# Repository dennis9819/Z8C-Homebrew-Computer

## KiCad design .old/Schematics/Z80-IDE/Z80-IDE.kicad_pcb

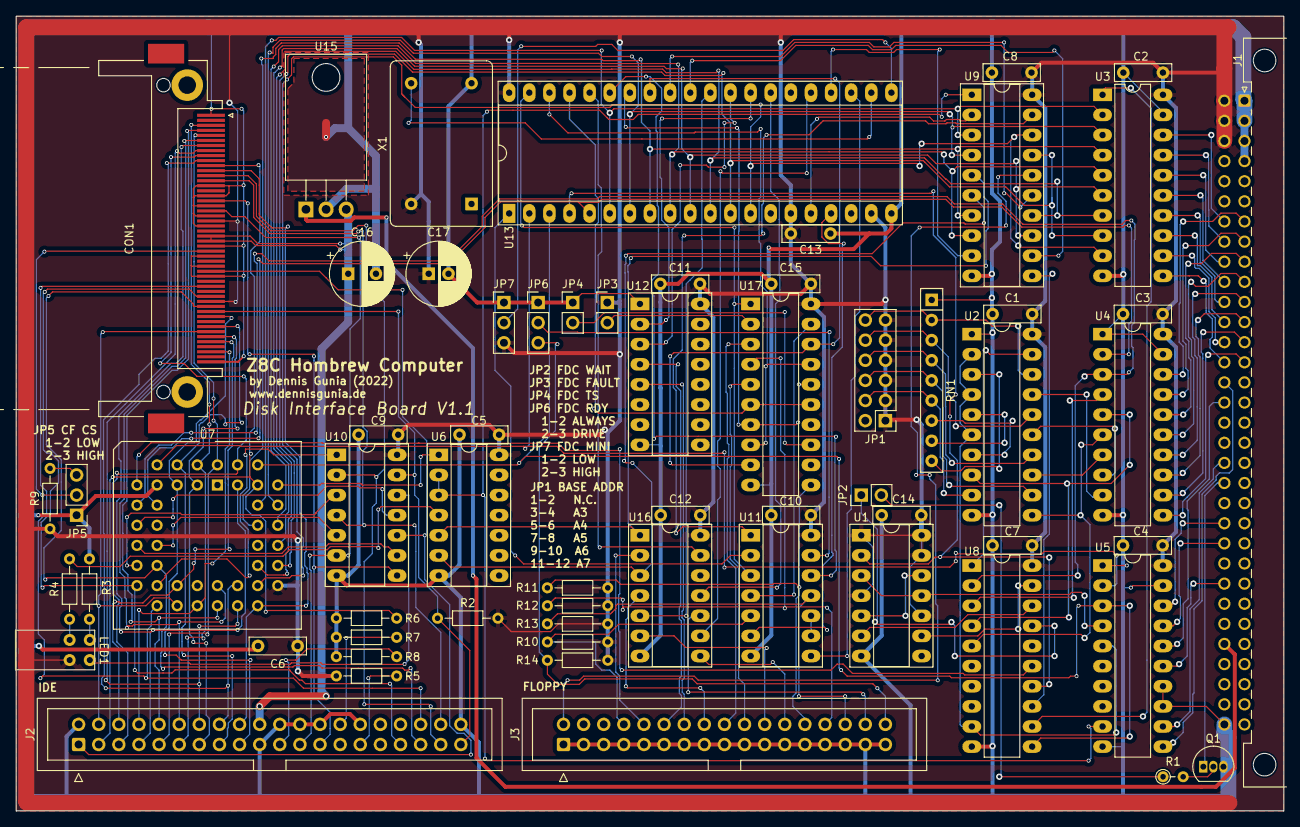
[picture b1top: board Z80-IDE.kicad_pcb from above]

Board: 2 copper layers, 160.0 x 100.3 mm, 62 parts (0 on the bottom side), 151 nets.

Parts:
C1, C2, C3, C4, C5, C6, C7, C8, C9, C10, C11, C12, C13, C14, C15: 100nF; C_Rect_L7.0mm_W2.0mm_P5.00mm
C16: 470uF; CP_Radial_D8.0mm_P3.50mm
C17: 100uF; CP_Radial_D8.0mm_P2.50mm
CON1: CF-CARD; CF-Card_3M_N7E50-E516xx-30
J1: Conn_02x32_Row_Letter_First; DIN41612_Q_2x32_Male_Horizontal_THT
J2: IDE Connector; IDC-Header_2x20_P2.54mm_Vertical
J3: Floppy Connector; IDC-Header_2x17_P2.54mm_Vertical
JP1: Conn_02x06_Odd_Even; PinHeader_2x06_P2.54mm_Vertical
JP2, JP3, JP4: Jumper_2_Bridged; PinHeader_1x02_P2.54mm_Vertical
JP5, JP6, JP7: Jumper_3_Open; PinHeader_1x03_P2.54mm_Vertical
LED1: MENOTR_A500_Dual_3mm; MENTOR A500 Dual 3mm
Q1: BC548; TO-92_Inline
R1: 220; R_Axial_DIN0204_L3.6mm_D1.6mm_P2.54mm_Vertical
R2, R3, R4, R5, R6, R7, R8, R9, R10, R11, R12, R13, R14: 10k; R_Axial_DIN0204_L3.6mm_D1.6mm_P7.62mm_Horizontal
RN1: R_Network08; R_Array_SIP9
U1: 74HC74; DIP-14_W7.62mm_Socket_LongPads
U2: 74LS688; DIP-20_W7.62mm_LongPads
U3, U4, U5: 74HC245; DIP-20_W7.62mm_LongPads
U6: 74HC02; DIP-14_W7.62mm_Socket_LongPads
U7: 82C55A_PLCC; PLCC-44_THT-Socket
U8: GAL16V8; DIP-20_W7.62mm_LongPads
U9: 74HCT273; DIP-20_W7.62mm_Socket_LongPads
U10, U16: 74HCT04; DIP-14_W7.62mm_Socket_LongPads
U11: 74HCT14; DIP-14_W7.62mm_Socket_LongPads
U12: 74HCT139; DIP-16_W7.62mm_Socket_LongPads
U13: FDC9266; DIP-40_W15.24mm_Socket_LongPads
U15: L7805; TO-220-3_Horizontal_TabDown
U17: 74HC240; DIP-20_W7.62mm_LongPads
X1: 8MHz; Oscillator_DIP-14

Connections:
+5V: C1.1, C2.1, C3.1, C4.1, C5.1, C6.1, C7.1, C8.1, C9.1, C10.1, C11.1, C12.1, C13.1, C14.1, C15.1, C17.1, CON1.36 (/WE), CON1.44 (/REG), J1.b1, J1.b2, J1.b3, JP1.1, JP1.3, JP1.5, JP1.7, JP1.9, JP1.11, JP3.1 (A), JP7.3 (B), LED1.2b (A), R2.2, R5.1, R9.1, R10.2, R11.2, R12.2, R13.2, R14.2, U1.1 (~R), U1.4 (~S), U1.10 (~S), U1.13 (~R), U1.14 (VCC), U2.20 (VCC), U3.20 (VCC), U4.20 (VCC), U5.20 (VCC), U6.14 (VCC), U7.29 (VCC), U8.20 (VCC), U9.20 (VCC), U10.14 (VCC), U11.14 (VCC), U12.16 (VCC), U13.15 (~DACK), U13.19 (TEST), U13.40 (VCC), U16.14 (VCC), U17.20 (VCC), X1.14 (Vcc)
+12V: J1.b28, U15.1 (IN)
/#A0: U4.2 (A0), U7.10 (A0), U13.5 (A0)
/#A1: U4.3 (A1), U7.9 (A1), U8.2 (I2)
/#A2: U4.4 (A2), U8.3 (I3)
/#A3: U2.8 (P3), U4.5 (A3), U8.4 (I4)
/#A4: U2.11 (P4), U4.6 (A4), U8.5 (I5)
/#A5: U2.13 (P5), U4.7 (A5)
/#A6: U2.15 (P6), U4.8 (A6)
/#A7: U2.17 (P7), U4.9 (A7)
/#CLK_CPU: U1.3 (C), U1.11 (C), U5.4 (A2)
/#D0: U3.2 (A0), U7.38 (D0), U9.3 (D0), U13.6 (DB0)
/#D1: U3.3 (A1), U7.37 (D1), U9.4 (D1), U13.7 (DB1)
/#D2: U3.4 (A2), U7.36 (D2), U9.7 (D2), U13.8 (DB2)
/#D3: U3.5 (A3), U7.35 (D3), U9.8 (D3), U13.9 (DB3)
/#D4: U3.6 (A4), U7.33 (D4), U9.13 (D4), U13.10 (DB4)
/#D5: U3.7 (A5), U7.32 (D5), U9.14 (D5), U13.11 (DB5)
/#D6: U3.8 (A6), U7.31 (D6), U9.17 (D6), U13.12 (DB6)
/#D7: U3.9 (A7), U7.30 (D7), U9.18 (D7), U13.13 (DB7)
/#RESET: U6.1, U7.39 (RESET)
/A0: J1.a7, U4.18 (B0)
/A1: J1.a8, U4.17 (B1)
/A2: J1.a9, U4.16 (B2)
/A3: J1.a10, U4.15 (B3)
/A4: J1.a11, U4.14 (B4)
/A5: J1.a12, U4.13 (B5)
/A6: J1.a13, U4.12 (B6)
/A7: J1.a14, U4.11 (B7)
/CLK_CPU: J1.b16, U5.16 (B2)
/CSEL: J2.28, R7.2
/D0: J1.b7, U3.18 (B0)
/D1: J1.b8, U3.17 (B1)
/D2: J1.b9, U3.16 (B2)
/D3: J1.b10, U3.15 (B3)
/D4: J1.b11, U3.14 (B4)
/D5: J1.b12, U3.13 (B5)
/D6: J1.b13, U3.12 (B6)
/D7: J1.b14, U3.11 (B7)
/DMACK: J2.29, R5.2
/DMARQ: J2.21, R8.2
/IDE_VCC: C16.1, CON1.13 (VCC2), CON1.38 (VCC1), J2.20, U15.3 (OUT)
/PA0: CON1.21 (D0), J2.17, U7.5 (PA0)
/PA1: CON1.22 (D1), J2.15, U7.4 (PA1)
/PA2: CON1.23 (D2), J2.13, U7.3 (PA2)
/PA3: CON1.2 (D3), J2.11, U7.2 (PA3)
/PA4: CON1.3 (D4), J2.9, U7.44 (PA4)
/PA5: CON1.4 (D5), J2.7, U7.43 (PA5)
/PA6: CON1.5 (D6), J2.5, U7.42 (PA6)
/PA7: CON1.6 (D7), J2.3, R6.2, U7.41 (PA7)
/PB0: CON1.47 (D8), J2.4, U7.20 (PB0)
/PB1: CON1.48 (D9), J2.6, U7.21 (PB1)
/PB2: CON1.49 (D10), J2.8, U7.22 (PB2)
/PB3: CON1.27 (D11), J2.10, U7.24 (PB3)
/PB4: CON1.28 (D12), J2.12, U7.25 (PB4)
/PB5: CON1.29 (D13), J2.14, U7.26 (PB5)
/PB6: CON1.30 (D14), J2.16, U7.27 (PB6)
/PB7: CON1.31 (D15), J2.18, U7.28 (PB7)
/PC0: CON1.20 (A0), J2.35, U7.16 (PC0)
/PC1: CON1.19 (A1), J2.33, U7.17 (PC1)
/PC2: CON1.18 (A2), J2.36, U7.18 (PC2)
/PC3: U7.19 (PC3), U10.1
/PC4: U7.15 (PC4), U10.3
/PC5: U7.14 (PC5), U10.5
/PC6: U7.13 (PC6), U10.9
/PC7: U7.11 (PC7), U10.11
/~#IOREQ: U2.2 (P0), U2.4 (P1), U2.6 (P2), U5.5 (A3), U8.9 (I9)
/~#RD: U5.2 (A0), U7.6 (~RD), U8.8 (I8), U13.2 (~RD)
/~#RESET: U5.9 (A7), U6.2, U6.3, U9.1 (~Mr)
/~#WR: U5.3 (A1), U7.40 (~WR), U8.11 (I10/~OE), U13.3 (~WR)
/~ACTIVE: CON1.45 (/DASP), J2.39, R2.1, U10.13
/~DCS0: CON1.7 (/CS0), J2.37, U10.2
/~DCS1: CON1.32 (/CS1), J2.38, U10.4
/~DIOR: CON1.34 (/IORD), J2.25, U10.8
/~DIOW: CON1.35 (/IOWR), J2.23, U10.6
/~DRESET: CON1.41 (/RESET), J2.1, U10.10
/~IOREQ: J1.b25, U5.15 (B3)
/~M1: J1.b19, U5.12 (B6)
/~RD: J1.b22, U5.18 (B0)
/~RESET: J1.b15, U5.11 (B7)
/~WAIT: J1.b20, Q1.1 (C)
/~WR: J1.b23, U5.17 (B1)
BUSDIR: U3.1 (A->B), U8.12 (IO8)
CS_FDC: U1.2 (D), U8.14 (IO6), U13.4 (~CS)
CS_IDE: U7.7 (~CS), U8.15 (IO5)
CS_LATCH: U8.13 (IO7), U9.11 (Cp)
FDC_FLT/TR0: U13.33 (FLT/TR0), U17.9 (2Y3), U17.18 (1Y0)
FDC_FR/STEP: U13.37 (FR/STEP), U17.6 (1A2), U17.15 (2A1)
FDC_HD: U13.27 (HD), U16.11
FDC_HDL: U13.36 (HDL), U16.13
FDC_INDEX: U11.6, U13.17 (IDX)
FDC_LCT/DIR: U13.38 (LCT/DIR), U17.8 (1A3), U17.17 (2A0)
FDC_MINI: JP7.2 (C), U13.21 (MINI)
FDC_P0: U9.15 (Q5), U13.32 (P2)
FDC_P1: U9.12 (Q4), U13.31 (P1)
FDC_P2: U9.9 (Q3), U13.24 (P0)
FDC_RDY: U11.12, U13.35 (RDY)
FDC_RESET: U11.2, U13.1 (RST)
FDC_RW/~SEEK: U11.4, U17.19 (2OE)
FDC_TC: U9.2 (Q0), U13.16 (TC)
FDC_US0: U12.3 (A1), U13.29 (US0)
FDC_US1: U12.2 (A0), U13.28 (US1)
FDC_WDOUT: U13.30 (WDOUT), U16.5
FDC_WE: U13.25 (WE), U16.9
FDC_WP/TS: U13.34 (WP/TS), U17.7 (2Y2), U17.16 (1Y1)
FDC_~DSKD: U11.8, U13.23 (~DSKD)
FDC_~FAULT: JP3.2 (B), U17.2 (1A0)
FDC_~RDY: JP6.2 (C), U11.13
FDC_~RW/SEEK: U11.3, U13.39 (~RW/SEEK), U17.1 (1OE)
FDC_~TS: JP4.2 (B), U17.13 (2A2)
FD_DENSEEL: J3.2, U9.16 (Q6)
FD_MOTEA: U6.5, U9.5 (Q1), U16.1
FD_MOTEB: U6.6, U9.6 (Q2), U16.3
FD_~ACTIVITY: R4.2, U6.4
FD_~DC/RDY: J3.34, JP6.3 (B), R14.1
FD_~DIR: J3.18, U17.3 (2Y0)
FD_~INDEX: J3.8, R10.1, U11.5
FD_~MOTEA: J3.10, U16.2
FD_~MOTEB: J3.16, U16.4
FD_~RDATA: J3.30, R13.1, U11.11
FD_~SIDE: J3.32, U16.10
FD_~STEP: J3.20, U17.5 (2Y1)
FD_~TRK0: J3.26, R11.1, U17.11 (2A3)
FD_~WDATA: J3.22, U16.6
FD_~WGATE: J3.24, U16.8
FD_~WRTPRO: J3.28, R12.1, U17.4 (1A1)
GND: C1.2, C2.2, C3.2, C4.2, C5.2, C6.2, C7.2, C8.2, C9.2, C10.2, C11.2, C12.2, C13.2, C14.2, C15.2, C16.2, C17.2, CON1.1 (GND1), CON1.8 (A10), CON1.9 (/ATASEL), CON1.10 (A9), CON1.11 (A8), CON1.12 (A7), CON1.14 (A6), CON1.15 (A5), CON1.16 (A4), CON1.17 (A3), CON1.50 (GND2), J1.a1, J1.a2, J1.a3, J1.a4, J1.b32, J2.2, J2.19, J2.22, J2.24, J2.26, J2.30, J2.40, J3.1, J3.3, J3.5, J3.7, J3.9, J3.11, J3.13, J3.15, J3.17, J3.19, J3.21, J3.23, J3.25, J3.27, J3.29, J3.31, J3.33, JP4.1 (A), JP5.1 (A), JP6.1 (A), JP7.1 (A), Q1.3 (E), R3.2, R6.1, R7.1, R8.1, RN1.1 (common), U1.7 (GND), U2.1 (G), U2.10 (GND), U3.10 (GND), U3.19 (CE), U4.1 (A->B), U4.10 (GND), U4.19 (CE), U5.1 (A->B), U5.10 (GND), U5.13 (B5), U5.14 (B4), U5.19 (CE), U6.7 (GND), U7.8 (GND), U8.10 (GND), U9.10 (GND), U10.7 (GND), U11.7 (GND), U12.1 (E), U12.8 (GND), U13.20 (GND), U15.2 (GND), U16.7 (GND), U17.10 (GND), X1.7 (GND)
unnamed: CON1.39 (/CSEL), JP5.2 (C)
unnamed: JP1.4, RN1.6 (R5), U2.9 (R3)
unnamed: JP1.6, RN1.5 (R4), U2.12 (R4)
unnamed: JP1.8, RN1.4 (R3), U2.14 (R5)
unnamed: JP1.10, RN1.3 (R2), U2.16 (R6)
unnamed: JP1.12, RN1.2 (R1), U2.18 (R7)
unnamed: JP2.1 (A), U8.17 (I03)
unnamed: JP2.2 (B), R1.1
unnamed: JP5.3 (B), R9.2
unnamed: LED1.1b (A), U10.12
unnamed: LED1.1a (K), R3.1
unnamed: LED1.2a (K), R4.1
unnamed: Q1.2 (B), R1.2
unnamed: RN1.7 (R6), U2.7 (R2)
unnamed: RN1.8 (R7), U2.5 (R1)
unnamed: RN1.9 (R8), U2.3 (R0)
unnamed: U1.5 (Q), U1.12 (D)
unnamed: U1.6 (~Q), U8.18 (IO2)
unnamed: U1.9 (Q), U8.19 (IO1)
unnamed: U2.19 (P=R), U8.1 (I1/CLK)
unnamed: U9.19 (Q7), U11.1
unnamed: U11.9, U11.10
unnamed: U13.22 (CLK), X1.8 (OUT)
~FD_DSA1: J3.12, U12.4 (O0)
~FD_DSB1: J3.14, U12.5 (O1)

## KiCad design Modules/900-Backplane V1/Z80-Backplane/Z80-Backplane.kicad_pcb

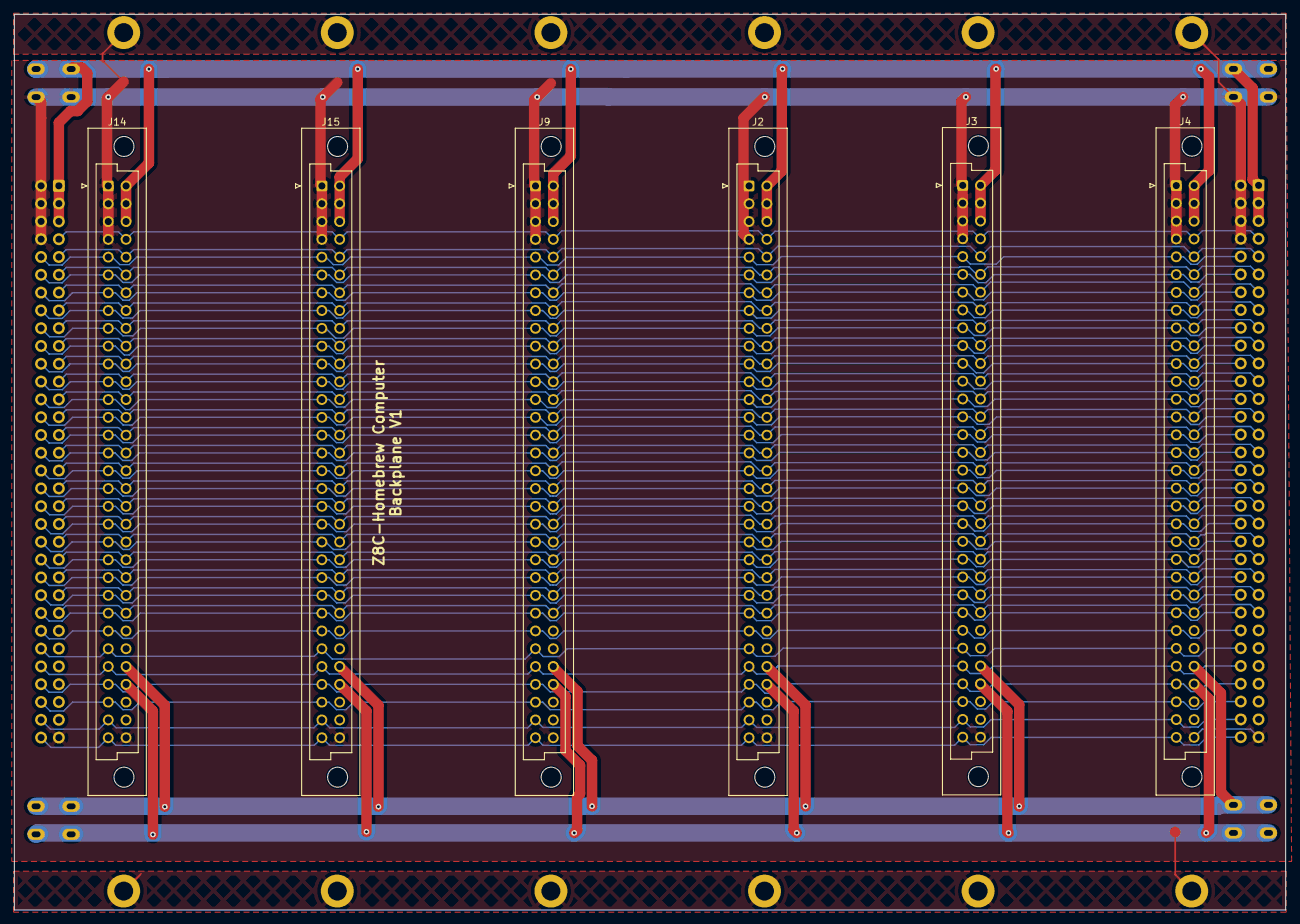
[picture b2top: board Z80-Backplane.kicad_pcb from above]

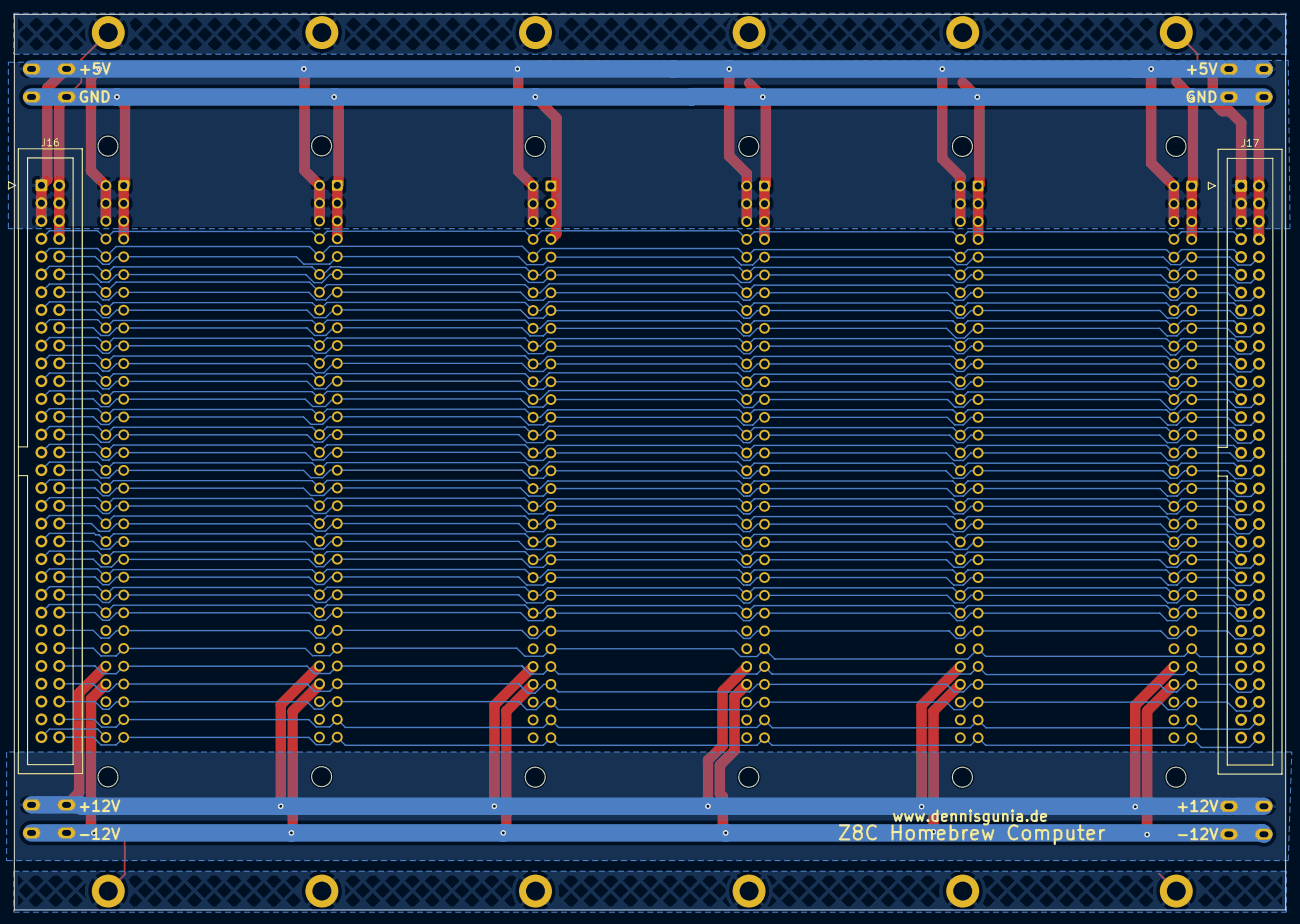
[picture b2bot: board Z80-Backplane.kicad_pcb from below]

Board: 2 copper layers, 181.4 x 127.8 mm, 28 parts (10 on the bottom side), 54 nets.

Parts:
H1, H2, H3, H4, H5, H6, H7, H8, H9, H10, H11, H12: MountingHole_Pad; MountingHole_2.7mm_M2.5_DIN965_Pad
J2, J3, J4, J9, J14, J15: Conn_02x32_Row_Letter_First; DIN41612_B_2x32_Female_Vertical_THT
J5, J6, J7, J8, J10, J11, J12, J13: Conn_01x01_Male; FS-P475
J16, J17: Conn_02x32_Odd_Even; IDC-Header_2x32_P2.54mm_Vertical

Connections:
+5V: J2.b1, J2.b2, J2.b3, J3.b1, J3.b2, J3.b3, J4.b1, J4.b2, J4.b3, J5.1, J6.1, J9.b1, J9.b2, J9.b3, J14.b1, J14.b2, J14.b3, J15.b1, J15.b2, J15.b3, J16.1, J16.3, J16.5, J17.1, J17.3, J17.5
+12V: J2.b28, J3.b28, J4.b28, J9.b28, J10.1, J11.1, J14.b28, J15.b28
-12V: J2.b29, J3.b29, J4.b29, J9.b29, J12.1, J13.1, J14.b29, J15.b29
/A0: J2.a7, J3.a7, J4.a7, J9.a7, J14.a7, J15.a7, J16.14, J17.14
/A1: J2.a8, J3.a8, J4.a8, J9.a8, J14.a8, J15.a8, J16.16, J17.16
/A2: J2.a9, J3.a9, J4.a9, J9.a9, J14.a9, J15.a9, J16.18, J17.18
/A3: J2.a10, J3.a10, J4.a10, J9.a10, J14.a10, J15.a10, J16.20, J17.20
/A4: J2.a11, J3.a11, J4.a11, J9.a11, J14.a11, J15.a11, J16.22, J17.22
/A5: J2.a12, J3.a12, J4.a12, J9.a12, J14.a12, J15.a12, J16.24, J17.24
/A6: J2.a13, J3.a13, J4.a13, J9.a13, J14.a13, J15.a13, J16.26, J17.26
/A7: J2.a14, J3.a14, J4.a14, J9.a14, J14.a14, J15.a14, J16.28, J17.28
/A8: J2.a15, J3.a15, J4.a15, J9.a15, J14.a15, J15.a15, J16.30, J17.30
/A9: J2.a16, J3.a16, J4.a16, J9.a16, J14.a16, J15.a16, J16.32, J17.32
/A10: J2.a17, J3.a17, J4.a17, J9.a17, J14.a17, J15.a17, J16.34, J17.34
/A11: J2.a18, J3.a18, J4.a18, J9.a18, J14.a18, J15.a18, J16.36, J17.36
/A12: J2.a19, J3.a19, J4.a19, J9.a19, J14.a19, J15.a19, J16.38, J17.38
/A13: J2.a20, J3.a20, J4.a20, J9.a20, J14.a20, J15.a20, J16.40, J17.40
/A14: J2.a21, J3.a21, J4.a21, J9.a21, J14.a21, J15.a21, J16.42, J17.42
/A15: J2.a22, J3.a22, J4.a22, J9.a22, J14.a22, J15.a22, J16.44, J17.44
/A16: J2.a25, J3.a25, J4.a25, J9.a25, J14.a25, J15.a25, J16.50, J17.50
/A17: J2.a26, J3.a26, J4.a26, J9.a26, J14.a26, J15.a26, J16.52, J17.52
/A18: J2.a27, J3.a27, J4.a27, J9.a27, J14.a27, J15.a27, J16.54, J17.54
/A19: J2.a28, J3.a28, J4.a28, J9.a28, J14.a28, J15.a28, J16.56, J17.56
/A20: J2.a29, J3.a29, J4.a29, J9.a29, J14.a29, J15.a29, J16.58, J17.58
/A21: J2.a30, J3.a30, J4.a30, J9.a30, J14.a30, J15.a30, J16.60, J17.60
/A22: J2.a31, J3.a31, J4.a31, J9.a31, J14.a31, J15.a31, J16.62, J17.62
/A23: J2.a32, J3.a32, J4.a32, J9.a32, J14.a32, J15.a32, J16.64, J17.64
/CLK_CPU: J2.b16, J3.b16, J4.b16, J9.b16, J14.b16, J15.b16, J16.31, J17.31
/D0: J2.b7, J3.b7, J4.b7, J9.b7, J14.b7, J15.b7, J16.13, J17.13
/D1: J2.b8, J3.b8, J4.b8, J9.b8, J14.b8, J15.b8, J16.15, J17.15
/D2: J2.b9, J3.b9, J4.b9, J9.b9, J14.b9, J15.b9, J16.17, J17.17
/D3: J2.b10, J3.b10, J4.b10, J9.b10, J14.b10, J15.b10, J16.19, J17.19
/D4: J2.b11, J3.b11, J4.b11, J9.b11, J14.b11, J15.b11, J16.21, J17.21
/D5: J2.b12, J3.b12, J4.b12, J9.b12, J14.b12, J15.b12, J16.23, J17.23
/D6: J2.b13, J3.b13, J4.b13, J9.b13, J14.b13, J15.b13, J16.25, J17.25
/D7: J2.b14, J3.b14, J4.b14, J9.b14, J14.b14, J15.b14, J16.27, J17.27
/MEMAQ: J2.a5, J3.a5, J4.a5, J9.a5, J14.a5, J15.a5, J16.10, J17.10
/~BUSACK: J2.a24, J3.a24, J4.a24, J9.a24, J14.a24, J15.a24, J16.48, J17.48
/~BUSREQ: J2.a23, J3.a23, J4.a23, J9.a23, J14.a23, J15.a23, J16.46, J17.46
/~HALT: J2.b21, J3.b21, J4.b21, J9.b21, J14.b21, J15.b21, J16.41, J17.41
/~INT0: J2.b4, J3.b4, J4.b4, J9.b4, J14.b4, J15.b4, J16.7, J17.7
/~INT1: J2.b5, J3.b5, J4.b5, J9.b5, J14.b5, J15.b5, J16.9, J17.9
/~INT2: J2.b6, J3.b6, J4.b6, J9.b6, J14.b6, J15.b6, J16.11, J17.11
/~INT3: J2.a6, J3.a6, J4.a6, J9.a6, J14.a6, J15.a6, J16.12, J17.12
/~INT: J2.b17, J3.b17, J4.b17, J9.b17, J14.b17, J15.b17, J16.33, J17.33
/~IOREQ: J2.b25, J3.b25, J4.b25, J9.b25, J14.b25, J15.b25, J16.49, J17.49
/~M1: J2.b19, J3.b19, J4.b19, J9.b19, J14.b19, J15.b19, J16.37, J17.37
/~MREQ: J2.b24, J3.b24, J4.b24, J9.b24, J14.b24, J15.b24, J16.47, J17.47
/~NMI: J2.b18, J3.b18, J4.b18, J9.b18, J14.b18, J15.b18, J16.35, J17.35
/~RD: J2.b22, J3.b22, J4.b22, J9.b22, J14.b22, J15.b22, J16.43, J17.43
/~RESET: J2.b15, J3.b15, J4.b15, J9.b15, J14.b15, J15.b15, J16.29, J17.29
/~WAIT: J2.b20, J3.b20, J4.b20, J9.b20, J14.b20, J15.b20, J16.39, J17.39
/~WR: J2.b23, J3.b23, J4.b23, J9.b23, J14.b23, J15.b23, J16.45, J17.45
GND: H1.1, H2.1, H3.1, H4.1, H5.1, H6.1, H7.1, H8.1, H9.1, H10.1, H11.1, H12.1, J2.a1, J2.a2, J2.a3, J2.a4, J2.b32, J3.a1, J3.a2, J3.a3, J3.a4, J3.b32, J4.a1, J4.a2, J4.a3, J4.a4, J4.b32, J7.1, J8.1, J9.a1, J9.a2, J9.a3, J9.a4, J9.b32, J14.a1, J14.a2, J14.a3, J14.a4, J14.b32, J15.a1, J15.a2, J15.a3, J15.a4, J15.b32, J16.2, J16.4, J16.6, J16.8, J16.63, J17.2, J17.4, J17.6, J17.8, J17.63

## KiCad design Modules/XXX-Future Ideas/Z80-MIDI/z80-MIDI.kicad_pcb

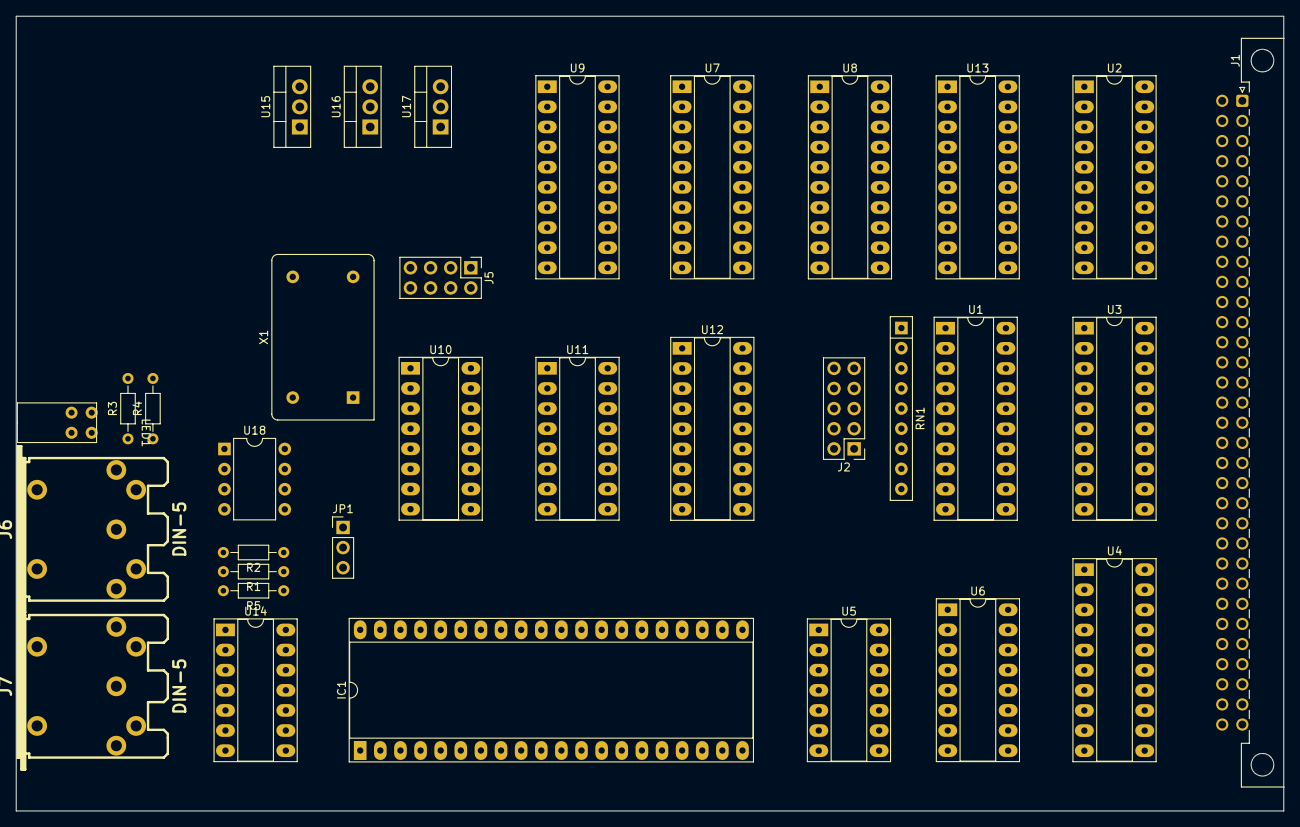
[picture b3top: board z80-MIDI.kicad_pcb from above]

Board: 2 copper layers, 160.0 x 100.3 mm, 33 parts (0 on the bottom side), 102 nets, no tracks yet.

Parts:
IC1: SIO0-DIP-40; DIP-40_W15.24mm_Socket_LongPads
J1: Conn_02x32_Row_Letter_First; DIN41612_Q_2x32_Male_Horizontal_THT
J2: Conn_02x05_Odd_Even; PinHeader_2x05_P2.54mm_Vertical
J5: Conn_02x04_Odd_Even; PinHeader_2x04_P2.54mm_Vertical
J6, J7: DIN-5; din-5
JP1: Jumper_3_Open; PinHeader_1x03_P2.54mm_Vertical
LED1: MENOTR_A500_Dual_3mm; MENTOR A500 Dual 3mm
R1, R2, R3, R4, R5: 10k; R_Axial_DIN0204_L3.6mm_D1.6mm_P7.62mm_Horizontal
RN1: R_Network08; R_Array_SIP9
U1: 74LS688; DIP-20_W7.62mm_Socket_LongPads
U2, U3, U4, U13: 74HC245; DIP-20_W7.62mm_Socket_LongPads
U5: 74HC02; DIP-14_W7.62mm_Socket_LongPads
U6: 74HC138; DIP-16_W7.62mm_Socket_LongPads
U7, U8, U9: 74LS573; DIP-20_W7.62mm_Socket_LongPads
U10: 74LS590; DIP-16_W7.62mm_Socket_LongPads
U11: 74HCT4051; DIP-16_W7.62mm_Socket_LongPads
U12: AD570; DIP-18_W7.62mm_Socket_LongPads
U14: 74LS06; DIP-14_W7.62mm_Socket_LongPads
U15: LM7915_TO220; TO-220-3_Vertical
U16: LM7810_TO220; TO-220-3_Vertical
U17: LM7910_TO220; TO-220-3_Vertical
U18: 6N137; DIP-8_W7.62mm
X1: 1MHz; Oscillator_DIP-14

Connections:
+5V: IC1.9 (+5V), J1.b1, J1.b2, J1.b3, J2.1, J2.3, J2.5, J2.7, J2.9, R1.1, R3.2, R4.2, R5.1, U1.20 (VCC), U2.20 (VCC), U3.20 (VCC), U4.20 (VCC), U5.14 (VCC), U6.16 (VCC), U7.20 (VCC), U8.20 (VCC), U9.20 (VCC), U10.10 (~MRC), U10.16 (VCC), U12.10 (VCC), U13.1 (A->B), U13.20 (VCC), U14.14 (VCC), U18.7 (EN), U18.8 (VCC), X1.14 (Vcc)
/#A0: IC1.34 (B/~A), U3.2 (A0), U6.1 (A0)
/#A1: IC1.33 (C/~D), U3.3 (A1), U6.2 (A1)
/#A2: U3.4 (A2), U5.8, U6.6 (E3)
/#A3: U1.8 (P3), U3.5 (A3)
/#A4: U1.11 (P4), U3.6 (A4)
/#A5: U1.13 (P5), U3.7 (A5)
/#A6: U1.15 (P6), U3.8 (A6)
/#A7: U1.17 (P7), U3.9 (A7)
/#CLK_CPU: IC1.20 (Φ), U4.4 (A2)
/#D0: IC1.40 (D0), U2.2 (A0), U7.19 (Q0), U8.2 (D0), U9.19 (Q0), U13.18 (B0)
/#D1: IC1.1 (D1), U2.3 (A1), U7.18 (Q1), U8.3 (D1), U9.18 (Q1), U13.17 (B1)
/#D2: IC1.39 (D2), U2.4 (A2), U7.17 (Q2), U8.4 (D2), U9.17 (Q2), U13.16 (B2)
/#D3: IC1.2 (D3), U2.5 (A3), U7.16 (Q3), U8.5 (D3), U9.16 (Q3), U13.15 (B3)
/#D4: IC1.38 (D4), U2.6 (A4), U7.15 (Q4), U8.6 (D4), U9.15 (Q4), U13.14 (B4)
/#D5: IC1.3 (D5), U2.7 (A5), U7.14 (Q5), U8.7 (D5), U9.14 (Q5), U13.13 (B5)
/#D6: IC1.37 (D6), U2.8 (A6), U7.13 (Q6), U8.8 (D6), U9.13 (Q6), U13.12 (B6)
/#D7: IC1.4 (D7), U2.9 (A7), U7.12 (Q7), U8.9 (D7), U9.12 (Q7), U13.11 (B7)
/A0: J1.a7, U3.18 (B0)
/A1: J1.a8, U3.17 (B1)
/A2: J1.a9, U3.16 (B2)
/A3: J1.a10, U3.15 (B3)
/A4: J1.a11, U3.14 (B4)
/A5: J1.a12, U3.13 (B5)
/A6: J1.a13, U3.12 (B6)
/A7: J1.a14, U3.11 (B7)
/CLK_CPU: J1.b16, U4.16 (B2)
/D0: J1.b7, U2.18 (B0)
/D1: J1.b8, U2.17 (B1)
/D2: J1.b9, U2.16 (B2)
/D3: J1.b10, U2.15 (B3)
/D4: J1.b11, U2.14 (B4)
/D5: J1.b12, U2.13 (B5)
/D6: J1.b13, U2.12 (B6)
/D7: J1.b14, U2.11 (B7)
//IOREQ: U1.2 (P0), U1.4 (P1), U1.6 (P2)
/~#IOREQ: IC1.36 (~IORQ), U4.5 (A3)
/~#M1: IC1.8 (~M1), U4.8 (A6)
/~#RD: IC1.32 (~RD), U4.2 (A0), U5.2, U6.3 (A2)
/~#RESET: IC1.21 (~RESET), U4.9 (A7)
/~INT: IC1.5 (~INT), J1.b17
/~IOREQ: J1.b25, U4.15 (B3)
/~M1: J1.b19, U4.12 (B6)
/~RD: J1.b22, U4.18 (B0)
/~RESET: J1.b15, U4.11 (B7)
/~WR: J1.b23, U4.17 (B1)
ADC_START: U8.16 (Q3), U12.11 (BLNK/~CONV)
BUF_POTAX: J5.1, U9.8 (D6)
BUF_POTAY: J5.3, U9.9 (D7)
BUF_POTBX: J5.5, U7.8 (D6)
BUF_POTBY: J5.7, U7.9 (D7)
DEC_BUF_DIR: U2.1 (A->B), U5.1
GND: IC1.31 (GND), J1.a1, J1.a2, J1.a3, J1.a4, J1.b32, J7.3, RN1.1 (common), U1.1 (G), U1.10 (GND), U2.10 (GND), U2.19 (CE), U3.1 (A->B), U3.10 (GND), U3.19 (CE), U4.1 (A->B), U4.10 (GND), U4.13 (B5), U4.14 (B4), U4.19 (CE), U5.7 (GND), U6.8 (GND), U7.10 (GND), U8.1 (OE), U8.10 (GND), U9.10 (GND), U10.8 (GND), U10.12 (~CE), U10.14 (~OE), U11.6 (~E), U11.8 (GND), U12.14 (ANALOG_COM), U12.15 (BIPOLAR), U12.16 (DIGITAL_COM), U13.10 (GND), U14.7 (GND), U18.5 (GND), X1.7 (GND)
MIDI_IN: IC1.12 (RXDA), JP1.1 (A), U14.5, U14.10
MIDI_OUT: IC1.15 (TXDA), JP1.3 (B), U14.9
MUX_0: U8.19 (Q0), U11.11 (S0)
MUX_1: U8.18 (Q1), U11.10 (S1)
MUX_2: U8.17 (Q2), U11.9 (S2)
unnamed: IC1.13 (~RXCA), IC1.14 (~TXCA), IC1.27 (~RxTxCB), U10.4 (Q4)
unnamed: J2.2, RN1.6 (R5), U1.9 (R3)
unnamed: J2.4, RN1.5 (R4), U1.12 (R4)
unnamed: J2.6, RN1.4 (R3), U1.14 (R5)
unnamed: J2.8, RN1.3 (R2), U1.16 (R6)
unnamed: J2.10, RN1.2 (R1), U1.18 (R7)
unnamed: J6.2, U18.3 (C)
unnamed: J6.4, U18.2 (A)
unnamed: J7.2, R2.2
unnamed: J7.4, R5.2
unnamed: JP1.2 (C), U14.3
unnamed: LED1.1a (K), U14.8
unnamed: LED1.1b (A), R3.1
unnamed: LED1.2a (K), U14.6
unnamed: LED1.2b (A), R4.1
unnamed: R1.2, U14.11, U18.6 (VO)
unnamed: R2.1, U14.2
unnamed: RN1.7 (R6), U1.7 (R2)
unnamed: RN1.8 (R7), U1.5 (R1)
unnamed: RN1.9 (R8), U1.3 (R0)
unnamed: U1.19 (P=R), U5.3, U5.9, U6.4 (E1), U6.5 (E2)
unnamed: U5.5, U5.6, U5.10
unnamed: U5.13, U8.11 (Load)
unnamed: U10.11 (CPC), U10.13 (CPR), X1.8 (OUT)
unnamed: U11.3 (A), U12.13 (ANALOG_IN)
unnamed: U12.2 (D7), U13.9 (A7)
unnamed: U12.3 (D6), U13.8 (A6)
unnamed: U12.4 (D5), U13.7 (A5)
unnamed: U12.5 (D4), U13.6 (A4)
unnamed: U12.6 (D3), U13.5 (A3)
unnamed: U12.7 (D2), U13.4 (A2)
unnamed: U12.8 (D1), U13.3 (A1)
unnamed: U12.9 (D0), U13.2 (A0)
unnamed: U14.1, U14.4
POTAX: J5.2, U11.13 (A0)
POTAY: J5.4, U11.14 (A1)
POTBX: J5.6, U11.15 (A2)
POTBY: J5.8, U11.12 (A3)
~ADC_RDY: U7.7 (D5), U9.7 (D5), U12.17 (~DATA_RDY)
~CS_SIO: IC1.35 (~CE), U5.4
~RD_ADC: U6.12 (O3), U13.19 (CE)
~RD_PORTA: U6.15 (O0), U9.1 (OE), U9.11 (Load)
~RD_PORTB: U6.14 (O1), U7.1 (OE), U7.11 (Load)
~WR_MUX: U5.11, U5.12, U6.9 (O6)
